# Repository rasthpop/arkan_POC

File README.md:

# Autonomous Radio-Beacon Coordinator for Air Reconnaissance and Warning (ARCAN)

## Software Usage

### Clean Target
```
cargo clean
```

### Build
```
cargo build --release
```
### Run
IMPORTANT: Pico has to be connected to your pc and the bootloader button on the mcu has to be press-held!
```
cargo run --release
```

### Log Data from Pico and Launch Terminal
```
sudo apt install tio
```
```
sudo tio /dev/ttyACM0
```

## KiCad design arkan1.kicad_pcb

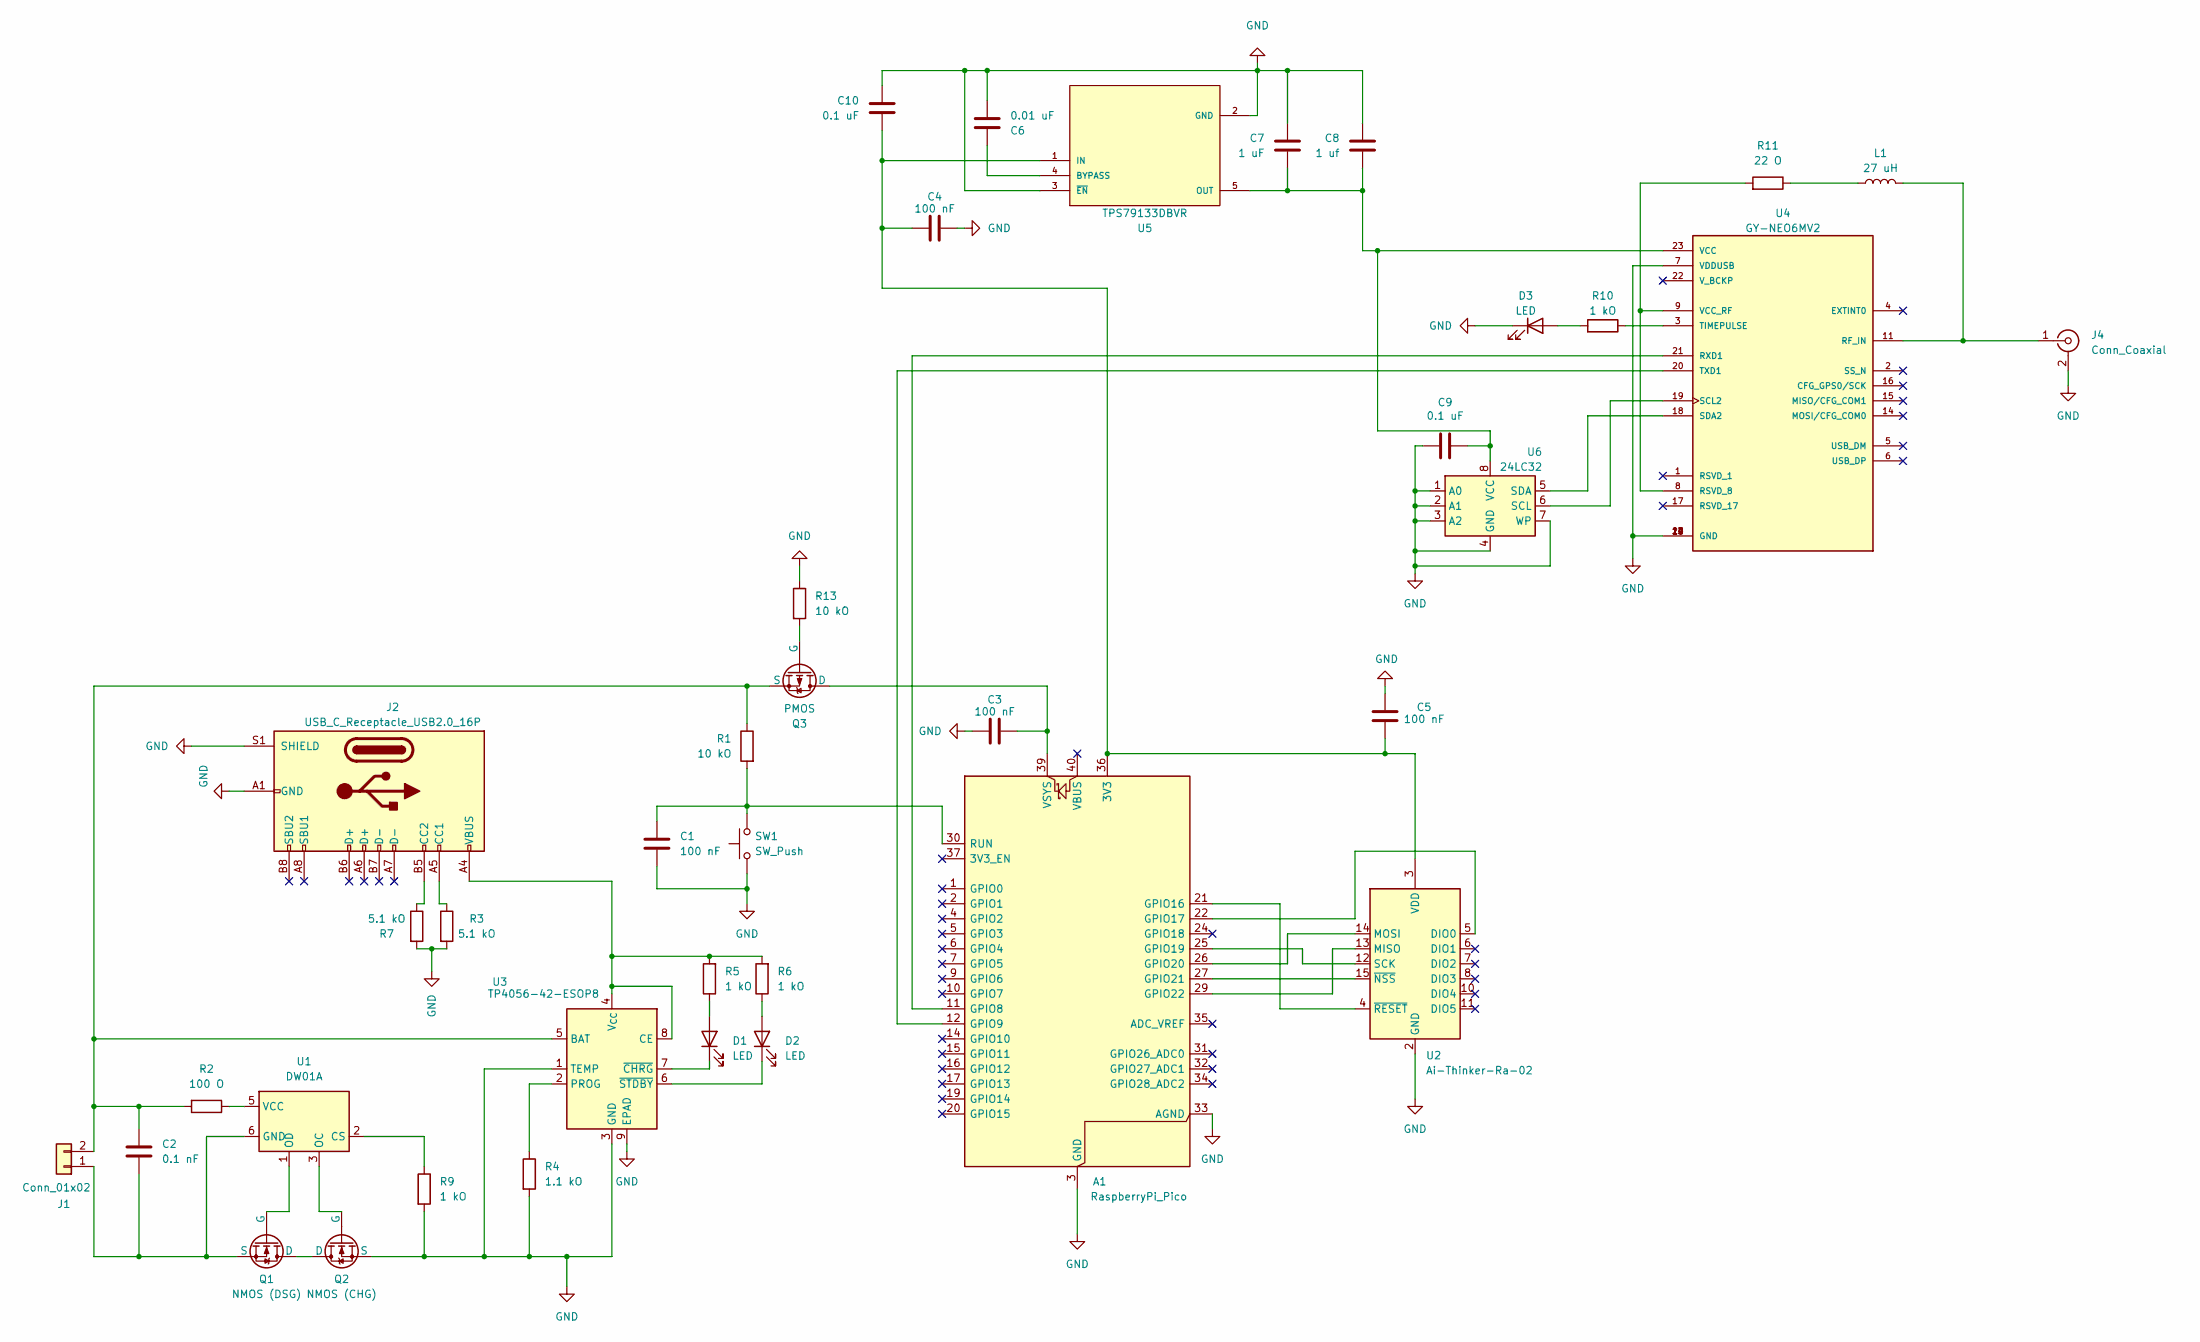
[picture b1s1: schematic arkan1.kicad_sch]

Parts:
A1: RaspberryPi_Pico; RaspberryPi_Pico_Common_SMD
C1, C3: 100 nF; C_0603_1608Metric
C2: 0.1 nF; C_0603_1608Metric
C4, C5: 100 nF; CP_EIA-7343-31_Kemet-D
C6: 0.01 uF; C_0603_1608Metric
C7: 1 uF; C_0603_1608Metric
C8: 1 uf; C_0603_1608Metric
C9, C10: 0.1 uF; C_0603_1608Metric
D1, D2, D3: LED; R_0805_2012Metric
J1: Conn_01x02; AMASS_XT30U-M_1x02_P5.0mm_Vertical
J2: USB_C_Receptacle_USB2.0_16P; USB_C_Receptacle_GCT_USB4105-xx-A_16P_TopMnt_Horizontal
J4: Conn_Coaxial; SMA_Molex_73251-1153_EdgeMount_Horizontal
L1: 27 uH; L_1210_3225Metric
Q1: NMOS (DSG); SOT-23
Q2: NMOS (CHG); SOT-23
Q3: PMOS; SOT-23
R1, R13: 10 kO; R_0805_2012Metric_Pad1.20x1.40mm_HandSolder
R2: 100 O; R_0805_2012Metric_Pad1.20x1.40mm_HandSolder
R3, R7: 5.1 kO; R_0805_2012Metric_Pad1.20x1.40mm_HandSolder
R4: 1.1 kO; R_0805_2012Metric_Pad1.20x1.40mm_HandSolder
R5, R6, R9, R10: 1 kO; R_0805_2012Metric_Pad1.20x1.40mm_HandSolder
R11: 22 O; R_0805_2012Metric_Pad1.20x1.40mm_HandSolder
SW1: SW_Push; SW_SPST_PTS645Sx43SMTR92
U1: DW01A; SOT-23-6
U2: Ai-Thinker-Ra-02; Ai-Thinker-Ra-01-LoRa
U3: TP4056-42-ESOP8; SOIC-8-1EP_3.9x4.9mm_P1.27mm_EP2.41x3.3mm_ThermalVias
U4: GY-NEO6MV2; XCVR_GY-NEO6MV2; PARTREV E
U5: TPS79133DBVR; SOT95P280X145-5N
U6: 24LC32; SOIC-8_3.9x4.9mm_P1.27mm

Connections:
unnamed: A1.36 (3V3), C4.2, C5.2, C10.1, U2.3 (VDD), U5.1 (IN)
unnamed: A1.11 (GPIO8), U4.21 (RXD1)
unnamed: A1.12 (GPIO9), U4.20 (TXD1)
unnamed: A1.21 (GPIO16), U2.4 (~RESET)
unnamed: A1.22 (GPIO17), U2.5 (DIO0)
unnamed: A1.25 (GPIO19), U2.12 (SCK)
unnamed: A1.26 (GPIO20), U2.14 (MOSI)
unnamed: A1.27 (GPIO21), U2.15 (~NSS)
unnamed: A1.29 (GPIO22), U2.13 (MISO)
unnamed: A1.30 (RUN), C1.1, R1.2, SW1.2
unnamed: A1.39 (VSYS), C3.2, Q3.1 (D)
unnamed: D1.2 (A), R5.1
unnamed: D1.1 (K), U3.7 (~CHRG)
unnamed: D2.2 (A), R6.1
unnamed: D2.1 (K), U3.6 (~STDBY)
unnamed: D3.2 (A), R10.2
unnamed: C2.2, J1.1, Q1.3 (S), U1.6 (GND)
unnamed: C2.1, J1.2, Q3.3 (S), R1.1, R2.2, U3.5 (BAT)
unnamed: J2.A5 (CC1), R3.1
unnamed: J2.B5 (CC2), R7.1
unnamed: J4.1 (In), L1.2, U4.11 (RF_IN)
unnamed: L1.1, R11.1
unnamed: Q1.1 (D), Q2.1 (D)
unnamed: Q1.2 (G), U1.1 (OD)
unnamed: Q2.2 (G), U1.3 (OC)
unnamed: Q3.2 (G), R13.2
unnamed: R9.1, U1.2 (CS)
unnamed: R2.1, U1.5 (VCC)
unnamed: J2.A4 (VBUS), J2.A9 (VBUS), J2.B4 (VBUS), J2.B9 (VBUS), R5.2, R6.2, U3.4 (V_{CC}), U3.8 (CE)
unnamed: R4.1, U3.2 (PROG)
unnamed: R11.2, U4.8 (RSVD_8), U4.9 (VCC_RF)
unnamed: U4.19 (SCL2), U6.6 (SCL)
unnamed: U4.18 (SDA2), U6.5 (SDA)
unnamed: R10.1, U4.3 (TIMEPULSE)
unnamed: C7.1, C8.1, C9.2, U4.23 (VCC), U5.5 (OUT), U6.8 (VCC)
unnamed: C6.1, U5.4 (BYPASS)

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
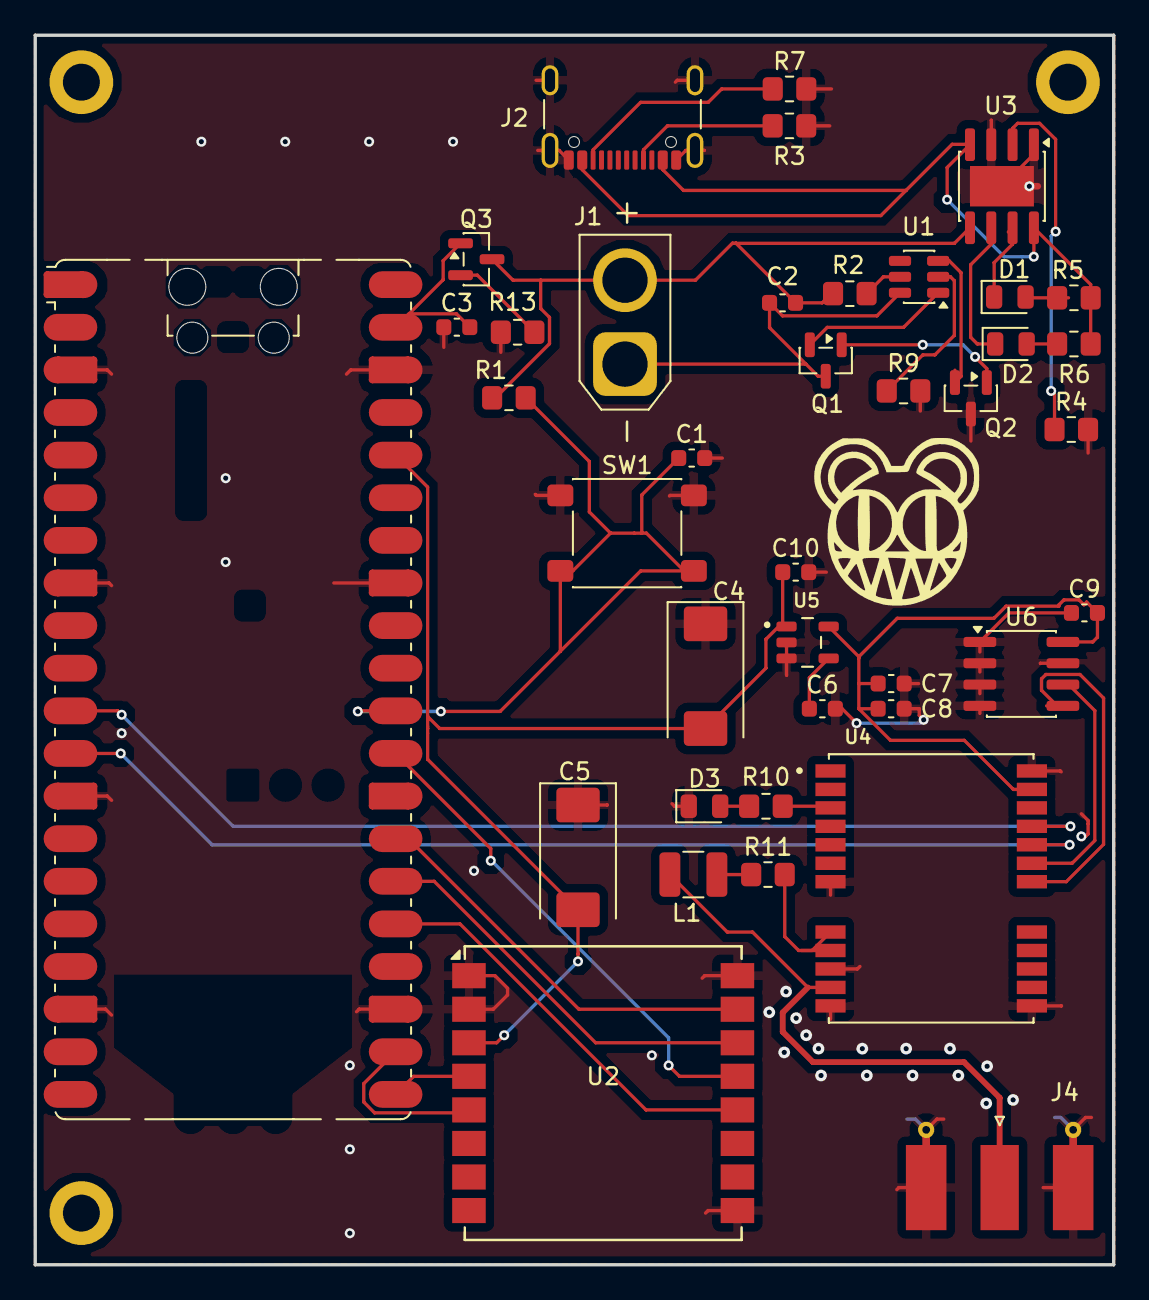
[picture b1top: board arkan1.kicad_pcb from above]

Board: 2 copper layers, 64.3 x 73.3 mm, 39 parts (0 on the bottom side), 37 nets.

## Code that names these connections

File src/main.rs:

#![no_std]
#![no_main]

use embedded_hal::serial::Read;
use embedded_hal::blocking::delay::DelayMs;
mod encryption;
// use crate::encryption::{CoordinateEncryptor, EncryptConfig, GpsCoord, MyCipher};

use embedded_hal::digital::v2::OutputPin;
use panic_halt as _;
use sx127x_lora::RadioMode;
mod gps_proccess;
use rp_pico::entry;
use rp_pico::hal::fugit::HertzU32;
use rp_pico::hal::{
    spi::Spi,
    clocks::{init_clocks_and_plls, Clock},
    pac,
    uart::{DataBits, StopBits, UartConfig, UartPeripheral},
    watchdog::Watchdog,
    Sio
};

mod sleep;
use sleep::{disable_uart1, enable_uart1, sleep_ms};

use usb_device::class_prelude::UsbBusAllocator;
use usbd_serial::SerialPort;
use usb_device::prelude::UsbVidPid;
use usb_device::prelude::UsbDeviceBuilder;
#[entry]
fn main() -> ! {
    let mut pac = pac::Peripherals::take().unwrap();
    let mut watchdog = Watchdog::new(pac.WATCHDOG);
    let clocks = init_clocks_and_plls(
        rp_pico::XOSC_CRYSTAL_FREQ,
        pac.XOSC,
        pac.CLOCKS,
        pac.PLL_SYS,
        pac.PLL_USB,
        &mut pac.RESETS,
        &mut watchdog,
    )
    .ok()
    .unwrap();
    let mut timer = rp_pico::hal::timer::Timer::new(pac.TIMER, &mut pac.RESETS, &clocks);

    let sio = Sio::new(pac.SIO);
    let core = pac::CorePeripherals::take().unwrap();
    let mut delay = cortex_m::delay::Delay::new(core.SYST, clocks.system_clock.freq().to_Hz());
    let pins = rp_pico::Pins::new(
        pac.IO_BANK0,
        pac.PADS_BANK0,
        sio.gpio_bank0,
        &mut pac.RESETS,
    );

    let usb_bus = UsbBusAllocator::new(rp_pico::hal::usb::UsbBus::new(
        pac.USBCTRL_REGS,
        pac.USBCTRL_DPRAM,
        clocks.usb_clock,
        true,
        &mut pac.RESETS,
    ));
    let mut serial = SerialPort::new(&usb_bus);
    let mut usb_dev = UsbDeviceBuilder::new(&usb_bus, UsbVidPid(0x16c0, 0x27dd))
        .device_class(2)
        .build();
    let spi_sck = pins.gpio18.into_function::<rp_pico::hal::gpio::FunctionSpi>();
    let spi_mosi = pins.gpio19.into_function::<rp_pico::hal::gpio::FunctionSpi>();
    let spi_miso = pins.gpio16.into_function::<rp_pico::hal::gpio::FunctionSpi>();
    let spi= Spi::new(
        pac.SPI0,
        (
            spi_mosi,
            spi_miso,
            spi_sck
        ),
    );
    let spi0:Spi<_,_,_,8> = spi.init(
        &mut pac.RESETS,
        clocks.peripheral_clock.freq(),
        HertzU32::Hz(2_000_000),
        embedded_hal::spi::MODE_0,
    );
    

    let mut nss = pins.gpio17.into_push_pull_output();
    nss.set_high().unwrap();
    let mut rst = pins.gpio20.into_push_pull_output();
    rst.set_low().unwrap();
    timer.delay_ms(20);
    rst.set_high().unwrap();
    timer.delay_ms(50);
    let mut lora = sx127x_lora::LoRa::new(
        spi0,
        nss,
        rst,
        433,
        delay
    ).expect("Could not connect to LoRa");
    let _ = lora.set_mode(sx127x_lora::RadioMode::Sleep).unwrap();
    timer.delay_ms(10);
    let _ = lora.set_tx_power(17, 1);
    let _ = lora.set_crc(true);
    let _ = lora.set_preamble_length(12);
    let _ = lora.set_ocp(120).unwrap();
    let _ = lora.set_coding_rate_4(8).unwrap();
    let _ = lora.set_spreading_factor(9);
    for _ in 0..100 {
        usb_dev.poll(&mut [&mut serial]);
        timer.delay_ms(10);
    }


    let mut led_pin = pins.led.into_push_pull_output();
    let uart_pins = (
        pins.gpio8.into_function::<rp_pico::hal::gpio::FunctionUart>(),//tx
        pins.gpio9.into_function::<rp_pico::hal::gpio::FunctionUart>()//rx
    );
    let mut uart = UartPeripheral::new(
        pac.UART1, 
        uart_pins, 
        &mut pac.RESETS)
        .enable(
            UartConfig::new(HertzU32::Hz(9600), DataBits::Eight, None, StopBits::One),
            clocks.peripheral_clock.freq()
        )
        .unwrap();
    let mut buf = [0u8; 128];
    let mut i = 0;
    let mut lora_buf = [0u8; 255];
    let mut last_lora_success: u64 = timer.get_counter().ticks();
    let mut first_lora_success: u64 = 0;
    let mut last_gps_success: u64 = 0;
    let mut last_lora_packet_len: usize = 0;
    loop {
        if usb_dev.poll(&mut [&mut serial]) {
            // todo
        }
        
        if let Ok(b) = uart.read() {
            if b == b'\n' {
                let line = &buf[..i];

                // if we found GPS signals, process and send to LoRa
                if let Some(len) = gps_proccess::gps_proccess(line, &mut serial, &mut lora_buf) {
                    last_gps_success = timer.get_counter().ticks();
                    last_lora_packet_len = len;

                    match lora.transmit_payload(lora_buf, last_lora_packet_len) {
                        Ok(_) => {
                            let _ = serial.write(b"sent data to LoRa\r\n");
                            last_lora_success = timer.get_counter().ticks();
                            if first_lora_success == 0 {
                                first_lora_success = last_lora_success;
                            }
                        },
                        Err(_) => { 
                            let _ = serial.write(b"ERR\r\n");
                        }
                    }

                // if GPS fix failed now, but we have valid data from before, resend it
                } else if last_lora_packet_len > 0 {
                    match lora.transmit_payload(lora_buf, last_lora_packet_len) {
                        Ok(_) => {
                            let _ = serial.write(b"sent data to LoRa\r\n");
                            last_lora_success = timer.get_counter().ticks();
                        },
                        Err(_) => { 
                            let _ = serial.write(b"ERR\r\n");
                        }
                    }
                }
                
                i = 0;
            } else if b == b'\r' {
                // ignore CR from CRLF
            } else if i < buf.len() {
                buf[i] = b;
                i += 1;
            } else {
                // buffer full: reset and store current byte as first byte
                i = 0;
                if !buf.is_empty() {
                    buf[0] = b;
                    i = 1;
                }
            }

            let now = timer.get_counter().ticks();

            // if we have been successfully sending data for 20 seconds, go to sleep
            if now.wrapping_sub(first_lora_success) > 20_000 && first_lora_success != 0 {
                let _ = serial.write(b"Been sending data for 20 seconds, going to sleep...\r\n");
                disable_uart1();
                let _ = led_pin.set_low();
                sleep_ms(&mut timer, 30_000); // sleep 30 seconds (testing, change later)
                enable_uart1();
                let _ = led_pin.set_high();

                let _ = serial.write(b"Woke up from sleep, retrying GPS connection...\r\n");
                first_lora_success = 0;
                last_lora_success = timer.get_counter().ticks();
            }

            // if we don't have any valid GPS data and did not send any packets, go to sleep and retry after
            if now.wrapping_sub(last_gps_success) > 30_000 && now.wrapping_sub(last_lora_success) > 30_000 {
                let _ = serial.write(b"No valid GPS data for 30 sec, going to sleep...\r\n");
                disable_uart1();
                let _ = led_pin.set_low();
                sleep_ms(&mut timer, 30_000); // sleep 30 s
                enable_uart1    ();
                let _ = led_pin.set_high();

                let _ = serial.write(b"Woke up from sleep, retrying GPS connection...\r\n");
                last_lora_success = timer.get_counter().ticks(); // reset this to avoid immediate sleep
            }

            // if we did not have GPS fix for 1 day, prevent resending irrelevant data
            if now.wrapping_sub(last_gps_success) > 86_400_000 && last_gps_success != 0 {
                last_lora_packet_len = 0;
            }
        }
    }
}

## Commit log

2025-10-08 Electric scheme
2025-10-24 init prj structure
2025-11-09 code to flash the pico LED
2025-11-10 uart1 data
2025-11-11 Initial commit
    Generated by react-native@0.82.1
2025-11-12 logging
2025-11-12 encryption template
2025-11-12 React Native app added
2025-11-12 reading data from GPS module
2025-11-12 Updated README, added version history
2025-11-12 Added version history
2025-11-12 implemented sleep routine and gps data parsing
2025-11-13 cleanup
2025-11-17 updated scheme + pcb
2025-11-17 updated pcb
2025-11-17 minor fix
2025-11-18 Fix Design Rules Check on PCB + SCH
2025-11-19 Added via stitches, via fence on pcb, isolated copper fix
    Also moved some components, added a small graphic on the pcb
2025-11-21 final pcb variant
2025-11-21 updated footprints for symbols, finalized
2025-11-29 basic LoRa init and transmit
2025-12-01 data transmittion
2025-12-01 init receiver cargo project
2025-12-03 receiver fix
2025-12-04 hotfix
2025-12-05 implemented decryption for receiver, and encryption for tranceiver. applied fixes for UART1 sleep (due to hard change from UART0 to UART1).
2025-12-07 demo-version
2025-12-07 some transmitter/receiver fixes
2025-12-10 update demo
2025-12-10 updated configuration
2025-12-10 Receiver coords output changed to compact JSON
2025-12-10 added advanced sleep scheduling and data sending strategy
2025-12-10 whoopsie
2025-12-11 App update to work reading coordinates from USB
2025-12-11 Add additional image to README
    Added a new image to the README for better visualization.
